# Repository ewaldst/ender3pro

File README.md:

# ender3pro
This is a collection of my upgrades to my Creality Ender 3 Pro

## cameraadapter
An adapter to mount a camera next to the printers display with a GoPro-style mount.

I have mounted a Raspberry Pi HQ Camera using the tripod socket

## daughterboard
A small board to be fitted on the Raspberry Pi's IO-Pins with the following features:

* Power supply for the RaspberryPi
* Power supply for up to 3 fans with separate DC-DC converter of choice
* PWM fan control for 3 fans (CASE1 + CASE2 are combined)
* Serial connection
* 1 3V3 digital input
* 1 DS18B20 sensor onboard
* 2 plugs for 2 more 1-wire sensors

## feet
Feet that I use for enough clearance on the bottom in combination with the raspi-case from this repo

foot.stl should be printed using PLA or any other rigid material
shoe.stl should be printed using TPU or any other flexible material

For mounting I used 2 M4x10 T-nuts and 2 M4x16 bolts for every foot

## hotendfan
Fan control script with systemd unit to run on the Raspberry Pi

## raspi-case
Rear mounted case for a SKR 1.4 (Turbo) mainboard, a 40x40 fan and a Raspberry Pi in combination with the 3DFused Y-axis linear rail kit. The case is inspired by the case from TeachingTech (thing:3688967)

The case consists of 4 parts to be easily printed on almost any 3D printer.

For the connection between the two bottom parts I used M3x20 bots and for the lid M3x4

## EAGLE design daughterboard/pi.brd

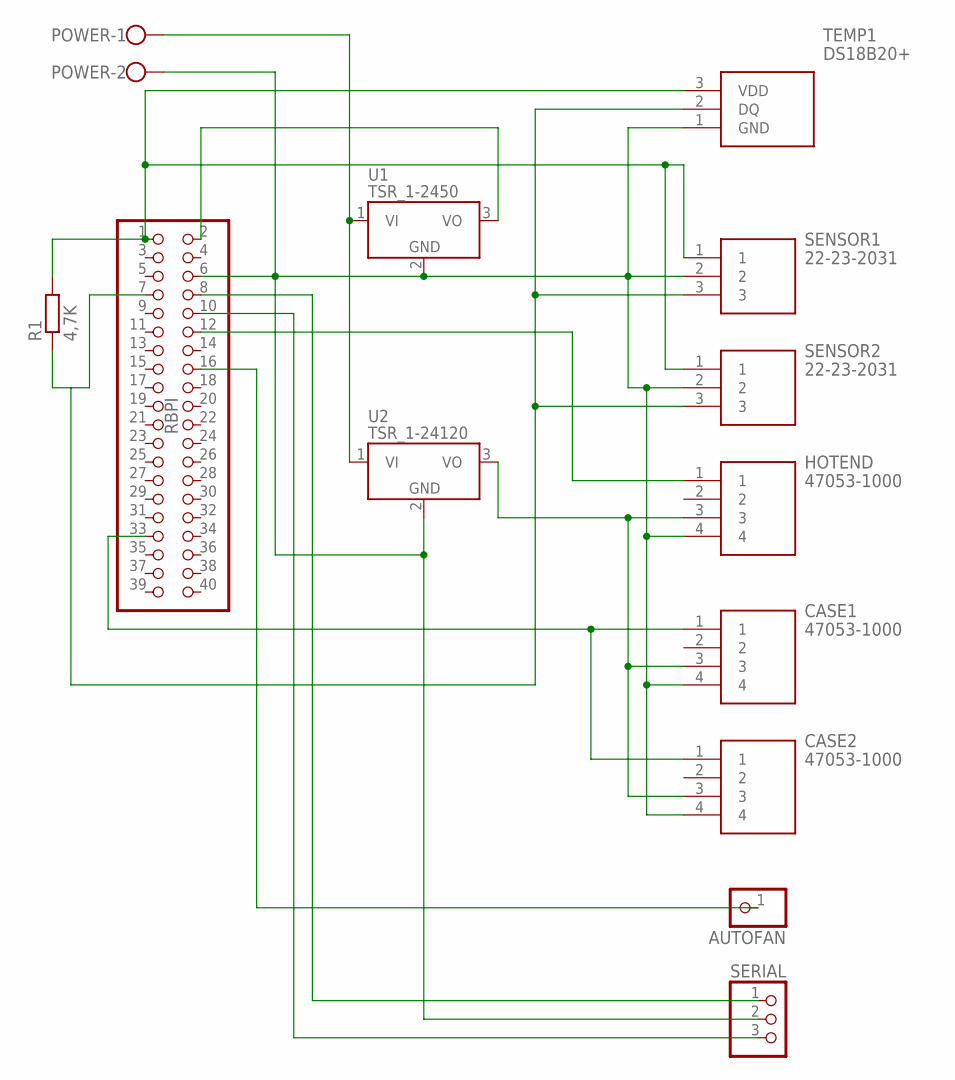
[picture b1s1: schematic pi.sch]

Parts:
AUTOFAN: PINHD-1X1; 1X01
CASE1, CASE2: 47053-1000
HOTEND: 47053-1000
POWER: W237-102
R1: 4,7K; 0411/12
RBPI: PINHD-2X20; 2X20
SENSOR1, SENSOR2: 22-23-2031; SHDR3W87P0X254_1X3_747X635X843
SERIAL: PINHD-1X3; 1X03
TEMP1: DS18B20+; TO-92
U1: TSR_1-2450; TSR-1
U2: TSR_1-24120; TSR-1

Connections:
unnamed: CASE1.4, CASE2.4, HOTEND.4, POWER.2, RBPI.6, SENSOR1.2, SENSOR2.2, SERIAL.2, TEMP1.1 (GND), U1.2 (GND), U2.2 (GND)
unnamed: RBPI.2, U1.3 (VO)
unnamed: CASE1.3, CASE2.3, HOTEND.3, U2.3 (VO)
unnamed: R1.2, RBPI.1, SENSOR1.1, SENSOR2.1, TEMP1.3 (VDD)
unnamed: R1.1, RBPI.7, SENSOR1.3, SENSOR2.3, TEMP1.2 (DQ)
unnamed: HOTEND.1, RBPI.12
unnamed: CASE1.1, CASE2.1, RBPI.33
unnamed: AUTOFAN.1, RBPI.16
unnamed: RBPI.8, SERIAL.1
unnamed: RBPI.10, SERIAL.3
VI: POWER.1, U1.1 (VI), U2.1 (VI)

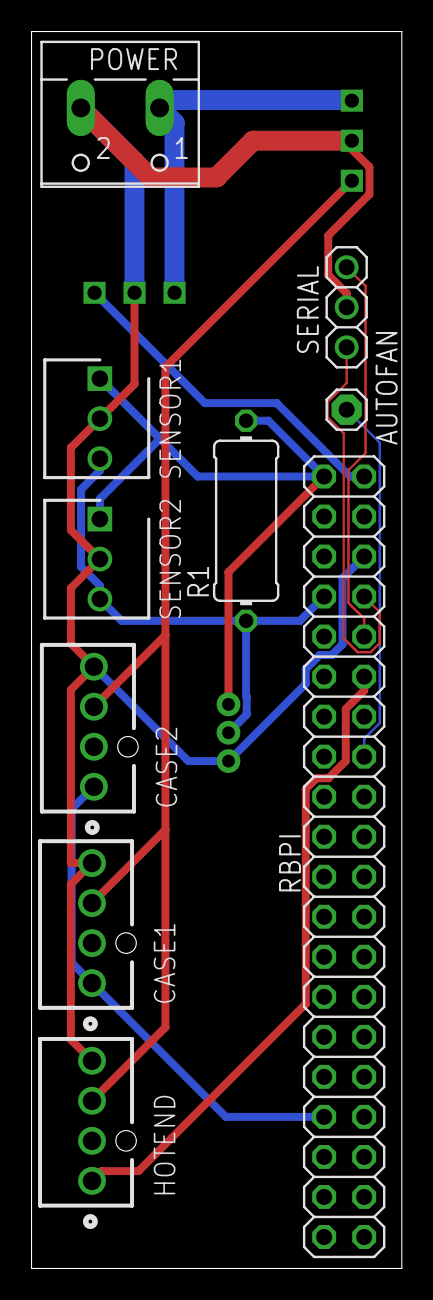
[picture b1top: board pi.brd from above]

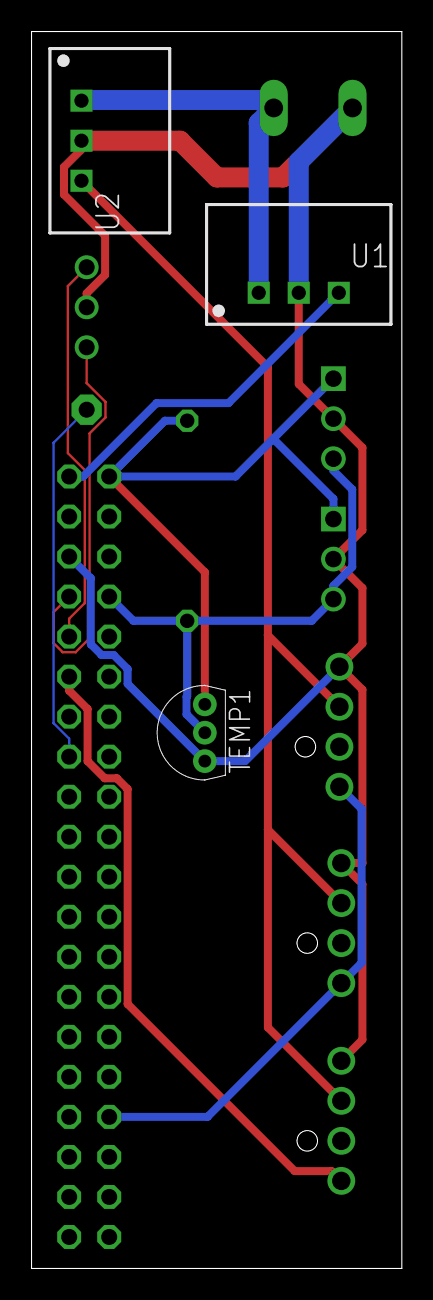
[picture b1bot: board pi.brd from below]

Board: 2 copper layers, 23.5 x 78.5 mm, 13 parts (3 on the bottom side), 11 nets.

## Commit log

2020-10-15 initial import
